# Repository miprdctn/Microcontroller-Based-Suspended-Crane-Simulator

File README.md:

This project is a learning project from the campus, which aims to improve the skills of fifth-semester students in the fields of electronic design and programming or IoT. In addition, it also improves teamwork skills because each person works on tasks that have been agreed upon by the team.

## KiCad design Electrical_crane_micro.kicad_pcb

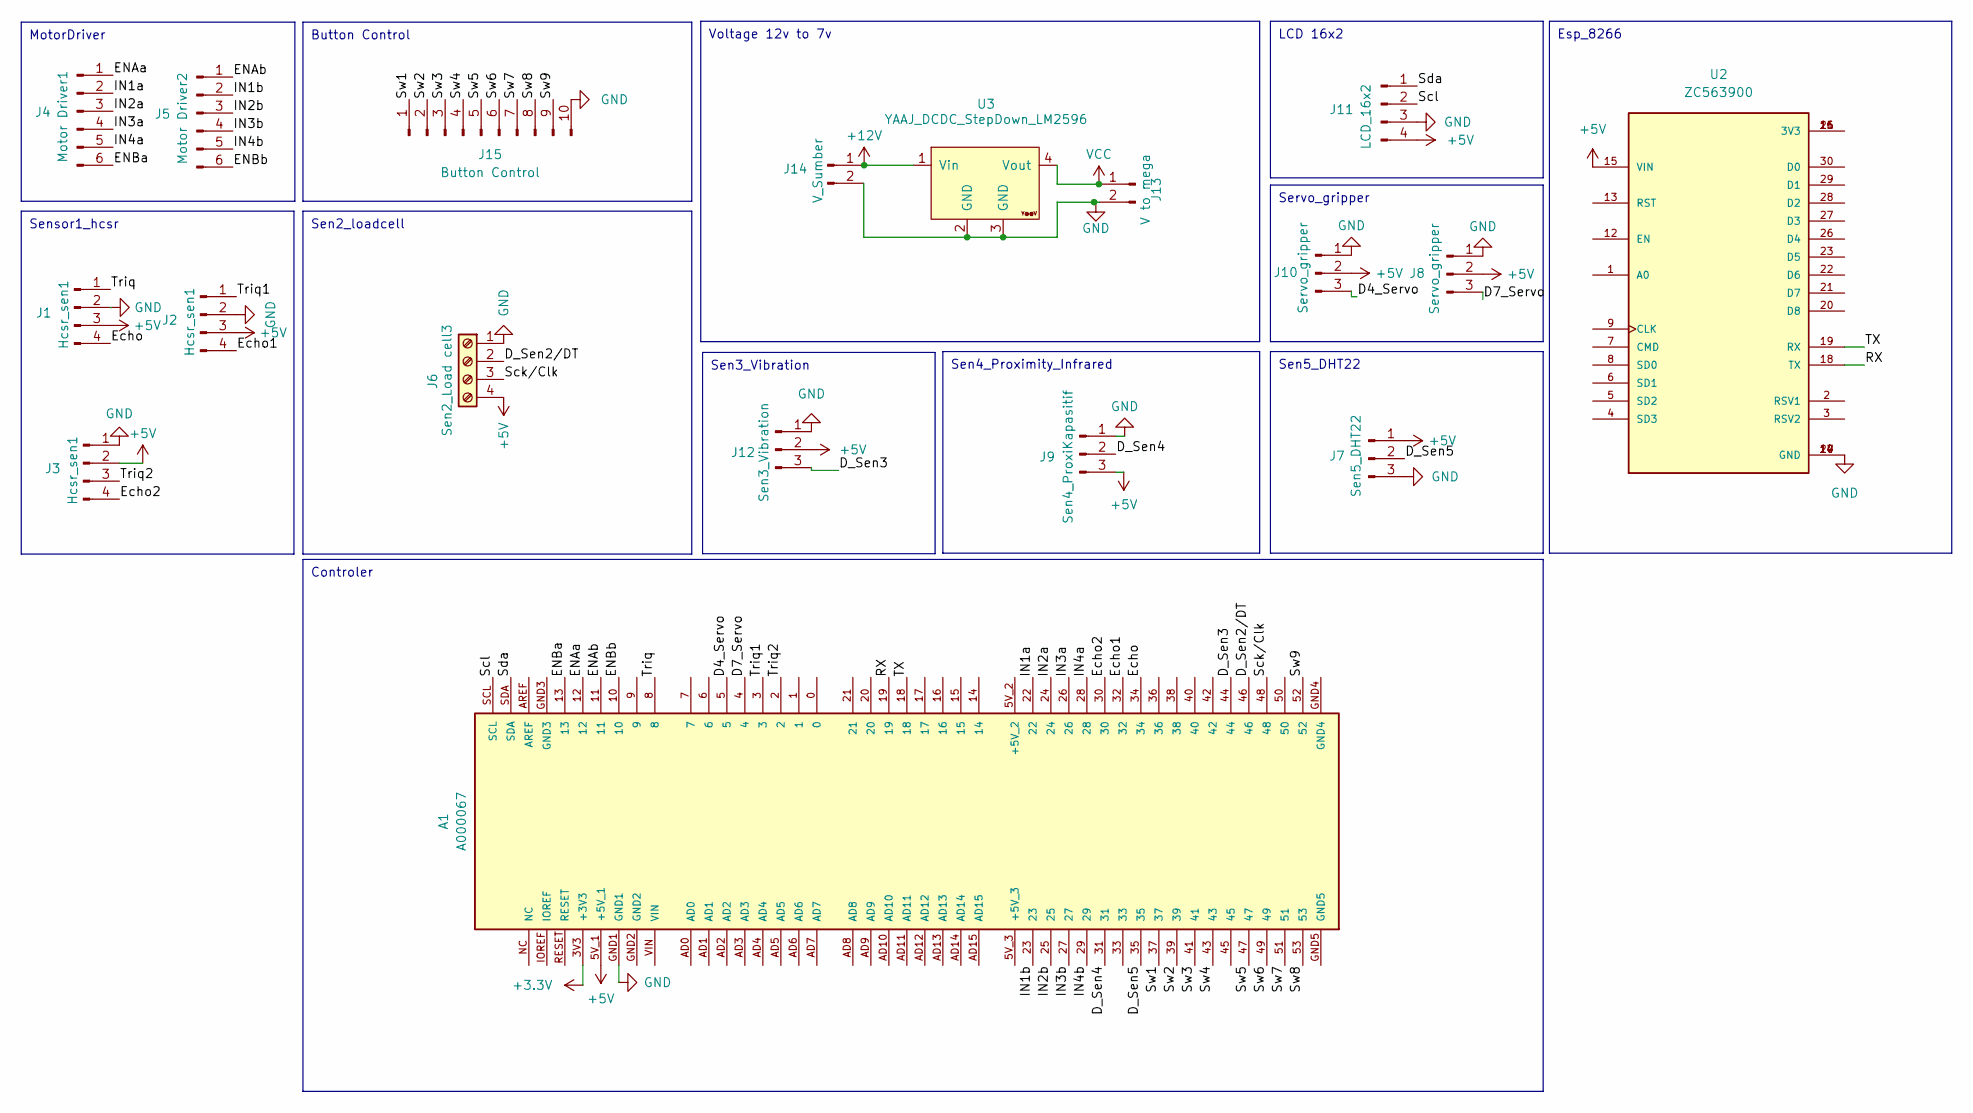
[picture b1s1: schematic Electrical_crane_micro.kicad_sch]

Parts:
A1: A000067; ARDUINO_A000067
J1, J2, J3: Hcsr_sen1; Molex_KK-254_AE-6410-04A_1x04_P2.54mm_Vertical
J4: Motor Driver1; Molex_KK-254_AE-6410-06A_1x06_P2.54mm_Vertical
J5: Motor Driver2; Molex_KK-254_AE-6410-06A_1x06_P2.54mm_Vertical
J6: Sen2_Load cell3; PinSocket_1x04_P2.54mm_Vertical
J7: Sen5_DHT22; PinSocket_1x03_P2.54mm_Vertical
J8, J10: Servo_gripper; Molex_KK-254_AE-6410-03A_1x03_P2.54mm_Vertical
J9: Sen4_ProxiKapasitif; Molex_KK-254_AE-6410-03A_1x03_P2.54mm_Vertical
J11: LCD_16x2; Molex_KK-254_AE-6410-04A_1x04_P2.54mm_Vertical
J12: Sen3_Vibration; Molex_KK-254_AE-6410-03A_1x03_P2.54mm_Vertical
J13: V to mega; TerminalBlock_Phoenix_MKDS-1,5-2-5.08_1x02_P5.08mm_Horizont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
J14: V_Sumber; TerminalBlock_Phoenix_MKDS-1,5-2-5.08_1x02_P5.08mm_Horizont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
J15: Button Control; Molex_KK-254_AE-6410-10A_1x10_P2.54mm_Vertical
U2: ZC563900; MODULE_ZC563900; PARTREV 1.0
U3: YAAJ_DCDC_StepDown_LM2596

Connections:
+3.3V: A1.3V3 (+3V3)
+5V: A1.5V_1 (+5V_1), J1.3, J2.3, J3.2, J6.4, J7.1, J8.2, J9.3, J10.2, J11.4, J12.2, U2.15 (VIN)
+12V: J14.1, U3.1 (Vin)
/D4_Servo: A1.5, J10.3
/D7_Servo: A1.4, J8.3
/D_Sen2/DT: A1.46, J6.2
/D_Sen3: A1.44, J12.3
/D_Sen4: A1.31, J9.2
/D_Sen5: A1.35, J7.2
/ENAa: A1.12, J4.1
/ENAb: A1.11, J5.1
/ENBa: A1.13, J4.6
/ENBb: A1.10, J5.6
/Echo: A1.34, J1.4
/Echo1: A1.32, J2.4
/Echo2: A1.30, J3.4
/IN1a: A1.22, J4.2
/IN1b: A1.23, J5.2
/IN2a: A1.24, J4.3
/IN2b: A1.25, J5.3
/IN3a: A1.26, J4.4
/IN3b: A1.27, J5.4
/IN4a: A1.28, J4.5
/IN4b: A1.29, J5.5
/RX: A1.19, U2.18 (TX)
/Sck/Clk: A1.48, J6.3
/Scl: A1.SCL, J11.2
/Sda: A1.SDA, J11.1
/Sw1: A1.37, J15.1
/Sw2: A1.39, J15.2
/Sw3: A1.41, J15.3
/Sw4: A1.43, J15.4
/Sw5: A1.47, J15.5
/Sw6: A1.49, J15.6
/Sw7: A1.51, J15.7
/Sw8: A1.53, J15.8
/Sw9: A1.52, J15.9
/TX: A1.18, U2.19 (RX)
/Triq: A1.8, J1.1
/Triq1: A1.3, J2.1
/Triq2: A1.2, J3.3
GND: A1.GND1, J1.2, J2.2, J3.1, J6.1, J7.3, J8.1, J9.1, J10.1, J11.3, J12.1, J13.2, J14.2, J15.10, U2.10 (GND), U2.14 (GND), U2.17 (GND), U2.24 (GND), U3.2 (GND), U3.3 (GND)
unnamed: U2.11 (3V3), U2.16 (3V3), U2.25 (3V3)
VCC: J13.1, U3.4 (Vout)

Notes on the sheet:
MotorDriver
LCD 16x2
Servo_gripper
Sen5_DHT22
Sen4_Proximity_Infrared
Sensor1_hcsr
Voltage 12v to 7v
Sen2_loadcell
Button Control
Controler
Esp_8266
Sen3_Vibration

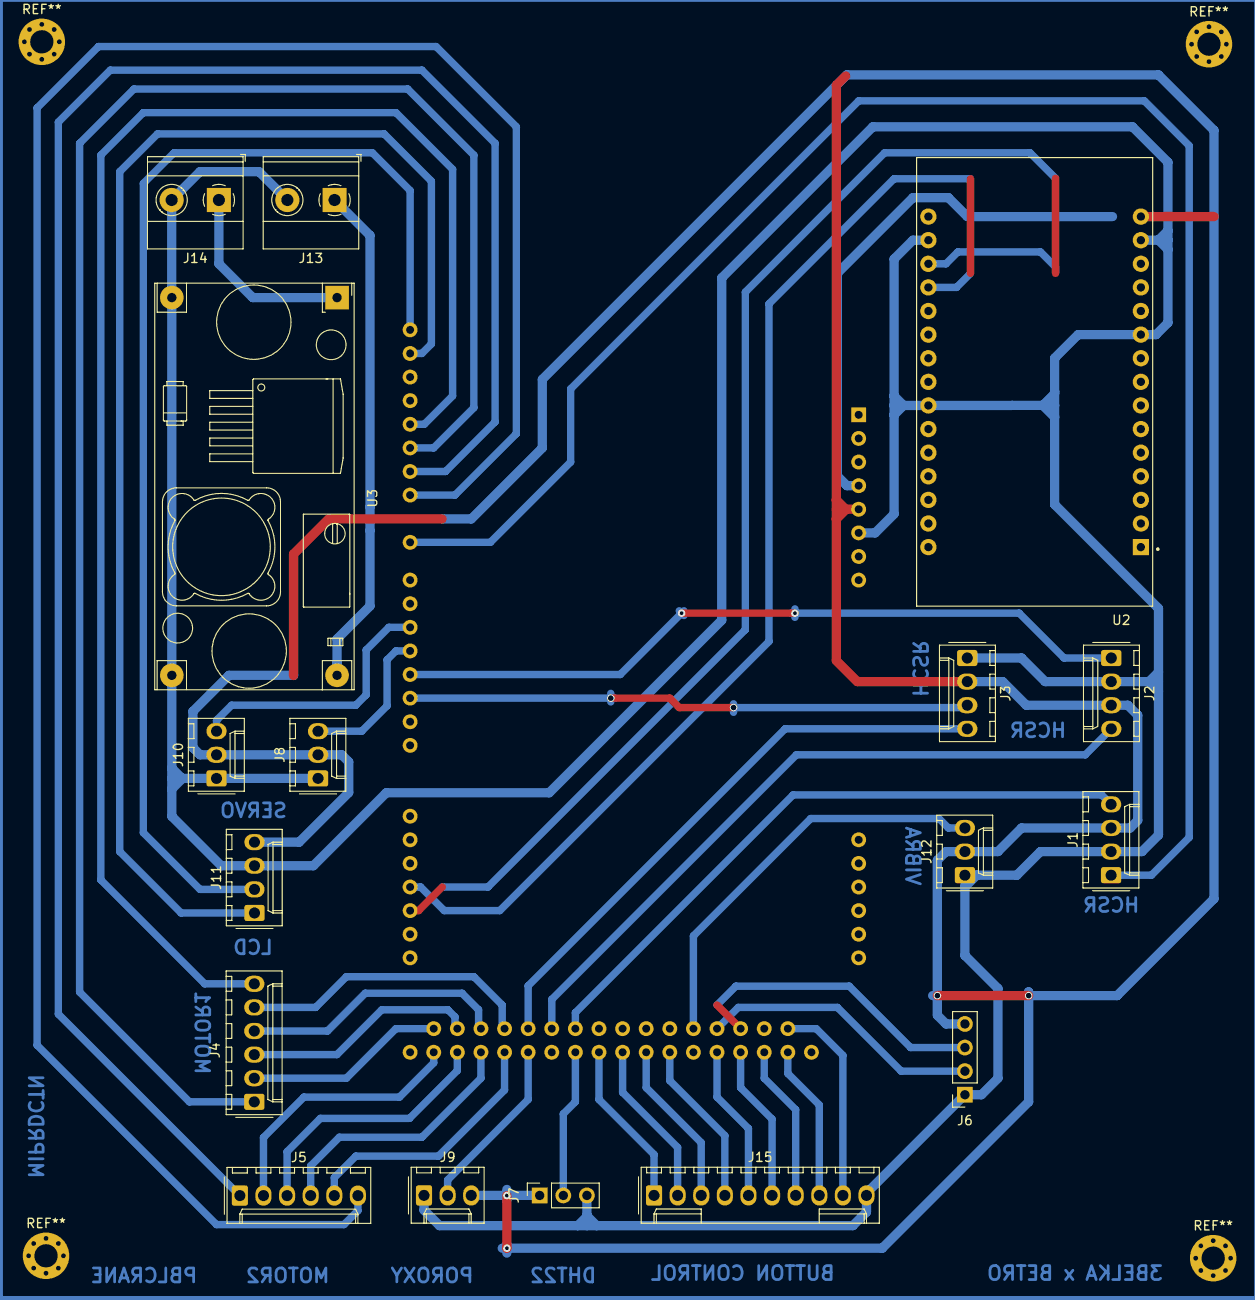
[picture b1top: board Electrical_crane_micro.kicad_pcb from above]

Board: 2 copper layers, 18 parts (1 on the bottom side), 43 nets.

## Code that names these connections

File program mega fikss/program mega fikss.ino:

//library 
#include <Servo.h>
#include <DHT.h>
#include <Wire.h>
#include <LiquidCrystal_I2C.h>
#include "HX711.h"

// Konfigurasi Servo
Servo myServo;
int potPin = A0;
int potValue = 0;
int servoAngle = 90;

// Konfigurasi DHT22
#define dht_pin 35
#define dht_type DHT22
DHT dht22(dht_pin, dht_type);

// Konfigurasi HCSR04
#define triq1 8
#define echo1 34
#define triq3 2
#define echo3 30
#define triq2 3
#define echo2 32

// Konfigurasi Sensor Getaran
#define VIBRATION_PIN 44
unsigned long lastVibrationTime = 0;
unsigned long vibrationInterval = 0;
unsigned long noVibrationTime = 0;
// int vibrationCount = 0;
float vibrationFrequency = 0;

// Konfigurasi HX711
#define DT 46
#define SCK 48
HX711 scale;
float calibration_factor = -81.0;

// Konfigurasi LCD
LiquidCrystal_I2C lcd(0x27, 20, 4);

// Konfigurasi button 
const int button1 = 39; //motor 1 kri
const int button2 = 47; //motor 1 kanan
const int button3 = 41; //motor 2 naik
const int button4 = 49; //motor 2 turun
const int buttonForward = 37; //maju
const int buttonBackward = 43; //mundur
//motor kri kanan (X)
const int motor1_in1 = 23; 
const int motor1_in2 = 25;
const int motor1_ena = 11;
//motor atas bawah (Y)
const int motor2_in3 = 27;
const int motor2_in4 = 29;
const int motor2_enb = 10;
//motor maju mundur(z)
const int motor_z_in1 = 22; 
const int motor_z_in2 = 24;
const int motor_z_ena = 12;

int x = 0; int y = 0; int z = 0;

// Timer untuk interval pembacaan sensor
unsigned long lastSensorReadTime = 0;
const unsigned long sensorInterval = 500; // Interval pembacaan sensor dalam ms

// Data sensor
float humi, temp, weight;
long jarakX, jarakY, jarakZ;

void setup() {
  Serial1.begin(115200); // Serial untuk komunikasi ke ESP8266
  Serial.begin(9600);  // Serial untuk debugging

  dht22.begin();

  pinMode(triq1, OUTPUT);
  pinMode(echo1, INPUT);
  pinMode(triq2, OUTPUT);
  pinMode(echo2, INPUT);
  pinMode(triq3, OUTPUT);
  pinMode(echo3, INPUT);
  pinMode(VIBRATION_PIN, INPUT_PULLUP);

  pinMode(button1, INPUT_PULLUP);
  pinMode(button2, INPUT_PULLUP);
  pinMode(button3, INPUT_PULLUP);
  pinMode(button4, INPUT_PULLUP);
  pinMode(buttonForward, INPUT_PULLUP);
  pinMode(buttonBackward, INPUT_PULLUP);

  pinMode(motor1_in1, OUTPUT);
  pinMode(motor1_in2, OUTPUT);
  pinMode(motor1_ena, OUTPUT);

  pinMode(motor2_in3, OUTPUT);
  pinMode(motor2_in4, OUTPUT);
  pinMode(motor2_enb, OUTPUT);

  pinMode(motor_z_in1, OUTPUT);
  pinMode(motor_z_in2, OUTPUT);
  pinMode(motor_z_ena, OUTPUT);

  myServo.attach(5);

  lcd.init();
  lcd.backlight();

  scale.begin(DT, SCK);
  scale.set_scale(calibration_factor);
  scale.tare();
}

void loop() {
  unsigned long currentMillis = millis();

  // Membaca sensor setiap interval
  if (currentMillis - lastSensorReadTime >= sensorInterval) {
    lastSensorReadTime = currentMillis;

    humi = dht22.readHumidity();
    temp = dht22.readTemperature();
    jarakX = readUltrasonic(triq1, echo1);
    jarakY = readUltrasonic(triq3, echo3);
    jarakZ = readUltrasonic(triq2, echo2);
    weight = scale.get_units();
    weight = (abs(weight) < 1.0) ? 0 : weight;

    updateVibration();

    // Menampilkan data di LCD
    lcd.setCursor(0, 0);
    lcd.print("H:" + String(humi, 1) + "% T:" + String(temp, 1) + "C");
    lcd.setCursor(0, 1);
    lcd.print("Berat: " + String(weight, 1) + " g");
    lcd.setCursor(0, 2);
    lcd.print("X:" + String(jarakX) + " Y:" + String(jarakY) + " Z:" + String(jarakZ));
    lcd.setCursor(0, 3);
    lcd.print("Vib:" + String(vibrationFrequency, 1));
    
    // delay(200);
    // Mengirim data ke ESP8266 berulang
    sendDataToESP8266();

    // Debugging data pada Serial Monitor
    Serial.println("=== Debugging Data ===");
    Serial.print("Humidity: "); Serial.print(humi); Serial.println("%");
    Serial.print("Temperature: "); Serial.print(temp); Serial.println(" C");
    Serial.print("Distance X: "); Serial.print(jarakX); Serial.println(" cm");
    Serial.print("Distance Y: "); Serial.print(jarakY); Serial.println(" cm");
    Serial.print("Distance Z: "); Serial.print(jarakZ); Serial.println(" cm");
    Serial.print("Weight: "); Serial.print(weight); Serial.println(" g");
    Serial.print("Vibration Frequency: "); Serial.print(vibrationFrequency); Serial.println(" Hz");
    // Serial.print("Vibration Count: "); Serial.println(vibrationCount);
    Serial.println("=====================");
  }

  // Mengatur servo
  potValue = analogRead(potPin);
  int mappedValue = map(potValue, 0, 1023, -90, 90);
  if (mappedValue > -10 && mappedValue < 10) {
    myServo.write(servoAngle);
  } else {
    servoAngle = constrain(servoAngle + mappedValue / 50, 0, 180);
    myServo.write(servoAngle);
  }

  // Membaca tombol dan mengontrol motor
  bool button1State = !digitalRead(button1);
  bool button2State = !digitalRead(button2);
  bool button3State = !digitalRead(button3);
  bool button4State = !digitalRead(button4);
  bool buttonForwardState = !digitalRead(buttonForward);
  bool buttonBackwardState = !digitalRead(buttonBackward);

  x = button1State ? -1 : button2State ? 1 : 0;
  y = button3State ? 1 : button4State ? -1 : 0;
  z = buttonForwardState ? 1 : buttonBackwardState ? -1 : 0;

  controlMotor1(x); controlMotor2(y); controlMotorZ(z);
}
// kirim data ke 8266
void sendDataToESP8266() {
  String jsonData = "{";
  jsonData += "\"humidity\":" + String(humi, 1) + ",";
  jsonData += "\"temperature\":" + String(temp, 1) + ",";
  jsonData += "\"distanceX\":" + String(jarakX) + ",";
  jsonData += "\"distanceY\":" + String(jarakY) + ",";
  jsonData += "\"distanceZ\":" + String(jarakZ) + ",";
  jsonData += "\"weight\":" + String(weight, 1) + ",";
  jsonData += "\"vibrationFrequency\":" + String(vibrationFrequency, 1) + ",";
  // jsonData += "\"vibrationCount\":" + String(vibrationCount);
  jsonData += "}";

  Serial1.println(jsonData);
}

long readUltrasonic(int trigPin, int echoPin) {
  digitalWrite(trigPin, LOW);
  delayMicroseconds(2);
  digitalWrite(trigPin, HIGH);
  delayMicroseconds(10);
  digitalWrite(trigPin, LOW);
  long duration = pulseIn(echoPin, HIGH);
  return (duration > 0) ? (duration / 2) / 29.1 : -1;
}

void updateVibration() {
  int vibrationValue = digitalRead(VIBRATION_PIN);
  unsigned long currentTime = micros();

  if (vibrationValue == HIGH) {
    if (currentTime - lastVibrationTime > 30) {//debounce time
      // vibrationCount++;
      vibrationInterval = currentTime - lastVibrationTime;
      lastVibrationTime = currentTime;
    }
    noVibrationTime = millis();
  } else {
    if (millis() - noVibrationTime > 2000) {
      vibrationInterval = 0;
      vibrationFrequency = 0;
      // vibrationCount = 0;
    }
  }

  if (vibrationInterval > 0) {
    vibrationFrequency = 1000000.0 / vibrationInterval;
  }
}
//motor kanan kiri
void controlMotor1(int state) {
  if (state == -1) {
    digitalWrite(motor1_in1, HIGH);
    digitalWrite(motor1_in2, LOW);
    analogWrite(motor1_ena, 100);//speed
  } else if (state == 1) {
    digitalWrite(motor1_in1, LOW);
    digitalWrite(motor1_in2, HIGH);
    analogWrite(motor1_ena, 100);//speed 
  } else {
    digitalWrite(motor1_in1, LOW);
    digitalWrite(motor1_in2, LOW);
  }
}
//motor naik turun
void controlMotor2(int state) {
  if (state == 1) {
    digitalWrite(motor2_in3, HIGH);
    digitalWrite(motor2_in4, LOW);
    analogWrite(motor2_enb, 80);//speed naik
  } else if (state == -1) {
    digitalWrite(motor2_in3, LOW);
    digitalWrite(motor2_in4, HIGH);
    analogWrite(motor2_enb, 50);//speed turun
  } else {
    digitalWrite(motor2_in3, LOW);
    digitalWrite(motor2_in4, LOW);
  }
}
//motor maju mundur
void controlMotorZ(int state) {
  if (state == 1) {
    digitalWrite(motor_z_in1, HIGH);
    digitalWrite(motor_z_in2, LOW);
    analogWrite(motor_z_ena, 200);//speed maju
  } else if (state == -1) {
    digitalWrite(motor_z_in1, LOW);
    digitalWrite(motor_z_in2, HIGH);
    analogWrite(motor_z_ena, 200);//speed mundur
  } else {
    digitalWrite(motor_z_in1, LOW);
    digitalWrite(motor_z_in2, LOW);
  }
}
